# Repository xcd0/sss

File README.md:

# sss

rp2040で作る分割キーボード

- 46キー
- 分割
- カラムスタッガード
- ロータリーエンコーダ
- 狭ピッチ（16.5mm）
- 小型(片手13cmx9cm)
- rp2040
- 3Dプリントケース
- 3Dプリント親指キーキャップ

## 完成予定

## 部品

### rp2040を使用した独自ボード

Raspberry Pi Pico が大きく自作キーボードで使いにくいため、同等のボードを作成した。  
とりあえず名前は安直にRPPslimとした。
[@74th](https://x.com/74th)さんの https://74th.booth.pm/items/3929664 が大変参考になった。  

- 30個のGPIO (Raspberry Pi Picoは23個、ProMicroは18個)
- USB-C
- キースイッチより狭い13.3x50mm (Raspberry Pi Picoは21x51mm)
	- GPIOが余分な場合、カットして13.3x30mmまで小さくして使用できる。
	- 上の写真の左は33mmでカットしている。この状態で17個GPIOを使用できる。
- ただし、GNDの数が少なく、両面実装で分厚く(5mm)、おそらく信頼性が低い。

普通rp2040を使用する自作キーボードは、キーボード本体にrp2040をそのまま実装する場合が多い。  
このsssではrp2040を別基板とし、キーボードに対して垂直に配置することでキーボードのサイズを小さくしている。  
また、別基板とすることで、別のキーボードを作る際にも使いまわせる、rp2040の部分に不具合があっても簡単に置き換えられる、ようにした。
 
### ロータリーエンコーダ

[アリエク](https://ja.aliexpress.com/item/1005006333962313.html)で売っているEVQWGD001という水平のロータリーエンコーダを使用。

### 親指用キーキャップ

 [booth](https://xcd0.booth.pm/items/4510462)に転がしている親指キーキャップの高さを少し高くしたものを使用。

### その他のキーキャップ

[Talp](https://talpkeyboard.net/items/5f5444c380933970d139e98c)さんで売っている0.8Uのキーキャップ。  
大体いつもこれを使っている。

## 設計
handwire予定だったが基板も作ることにした。choc対応をやめたら基板がすっきりして作りやすかった。  
### 回路図

### PCB

## ファームウェアのビルド

[tinygo](https://tinygo.org/)と[tinygo-keyboard](https://github.com/sago35/tinygo-keyboard)を使用している。  

Linuxはディストリビューションごとに方法があるので、<https://tinygo.org/getting-started/install/linux/>を参照。  
Macはhomebrewで入る模様。未確認。<https://tinygo.org/getting-started/install/macos/>  

windowsの場合、<https://tinygo.org/getting-started/install/windows/>にある通り、  
[scoop](https://scoop.sh/)経由でコンパイラをインストールするのが良い。

scoopはpowershellで下記のようにインストールできる。
```pwsh
Set-ExecutionPolicy -ExecutionPolicy RemoteSigned -Scope CurrentUser
Invoke-RestMethod -Uri https://get.scoop.sh | Invoke-Expression
```

後は下記のコマンドで、

```pwsh
scoop install go
scoop install tinygo
scoop install make
```
でコンパイラとmakeをインストールし、

```pwsh
cd src
make
```

でコンパイルできる。

## ファームウェアの書き込み

makefileに書いているため、

```
make flash
```

でビルドしつつ書き込むことができる。  
windowsのwslでは書き込めないので注意。  
powershellやmsysからも書き込める。  
BOOTボタンを押しながら抜き差しする必要はない。  

## キーマップ

goのソースコードに定義するとgofmtでフォーマットされて整列した状態を保てないため、  
[hjson形式](https://hjson.github.io/)で記述し、それをビルド前に解釈してキーマップを返す関数を自動生成するようにしている。  
<./src/script/prebuild/prebuild.go>にビルド前に実行されるコードがある。  

- キーマップ内のキーコードは<https://github.com/sago35/tinygo-keyboard/tree/main/keycodes>にあるものを使用する。  
- `lang`に定義した言語を表す文字列がそのままpackage名として使用される。まあ現状jpしかないけれども。  
- 短縮表現を`define`に定義できるようにした。
- `layout`にはレイヤーごとにキーコードを記載する。
	- これは単純に、`[][]string`として読み込まれ、`,`と`\n`区切りの単純な`[][][]string`に解釈される。

```hjson
# キーマップで使用する言語
lang: jp

# キーマップで使用するキーコードの短縮形定義
define: {
	LSFT: KeyLeftShift
	LCTL: KeyLeftCtrl
	LALT: KeyLeftAlt
}

# キーマップ
# レイヤーごとに記述する。
layout: [
	[ # layer 0
		KeyEsc,      Key1,        Key2,        Key3,        Key4,        Key5,        Key6,      Key7,        Key8,        Key9,        Key0,        KeyMinus,    KeyHat,        KeyBackslash,
		KeyTab,      KeyQ,        KeyW,        KeyE,        KeyR,        KeyT,        KeyY,      KeyU,        KeyI,        KeyO,        KeyP,        KeyAt,       KeyLeftBrace,  KeyBackspace,
		LCTL,        KeyA,        KeyS,        KeyD,        KeyF,        KeyG,        KeyH,      KeyJ,        KeyK,        KeyL,        KeySemicolon,KeyColon,    KeyRightBrace, KeyEnter,
		LSFT,        KeyZ,        KeyX,        KeyC,        KeyV,        KeyB,        KeyN,      KeyM,        KeyComma,    KeyPeriod,   KeySlash,    KeyBackslash2,KeyUp,        KeyRightShift,
		KeyMod1,     KeyHankaku,  KeyWindows,  LALT,        KeyMuhenkan, KeySpace,    KeySpace,  KeyHenkan,   KeyHiragana, KeyLeftAlt,  KeyMod1,     KeyLeft,     KeyDown,       KeyRight,
	]
```

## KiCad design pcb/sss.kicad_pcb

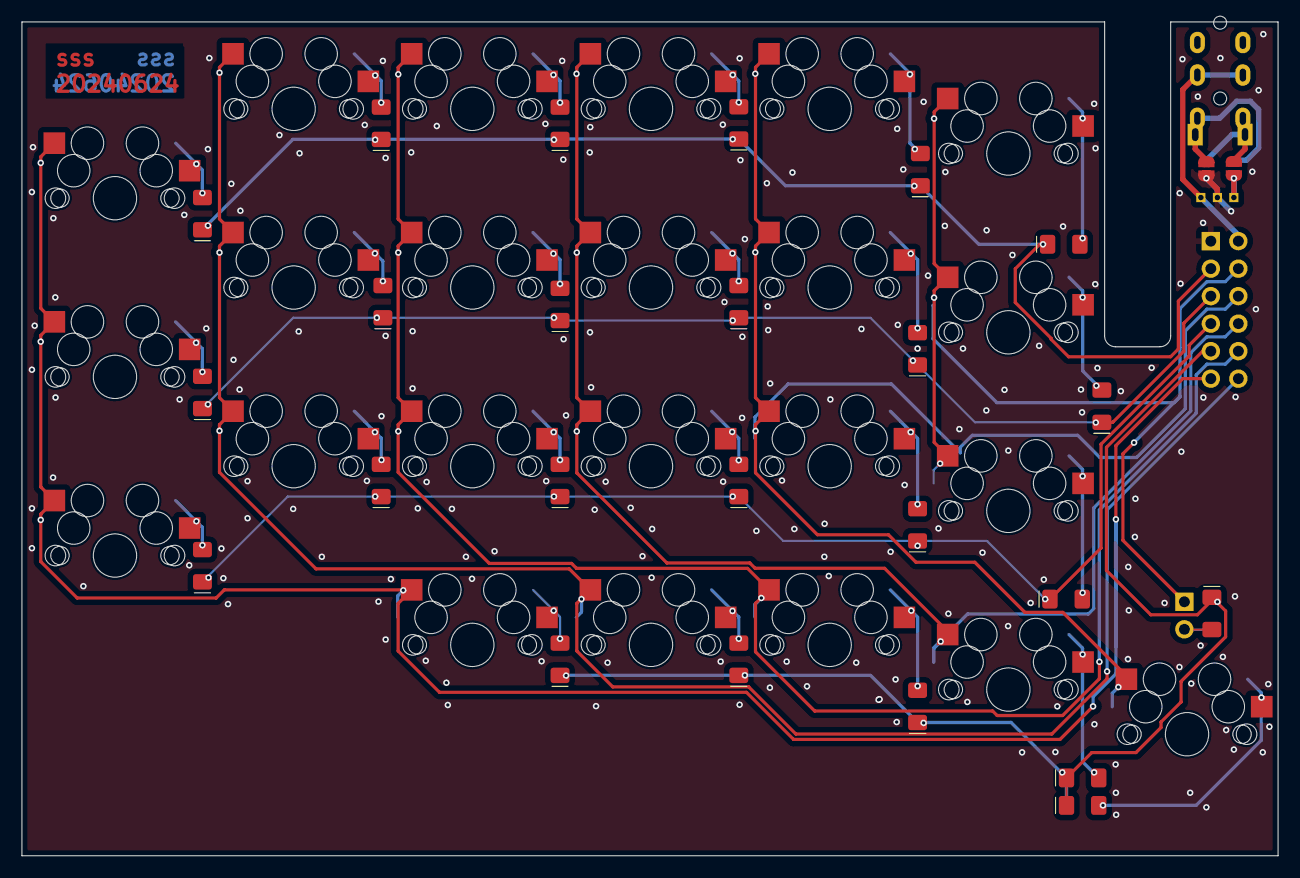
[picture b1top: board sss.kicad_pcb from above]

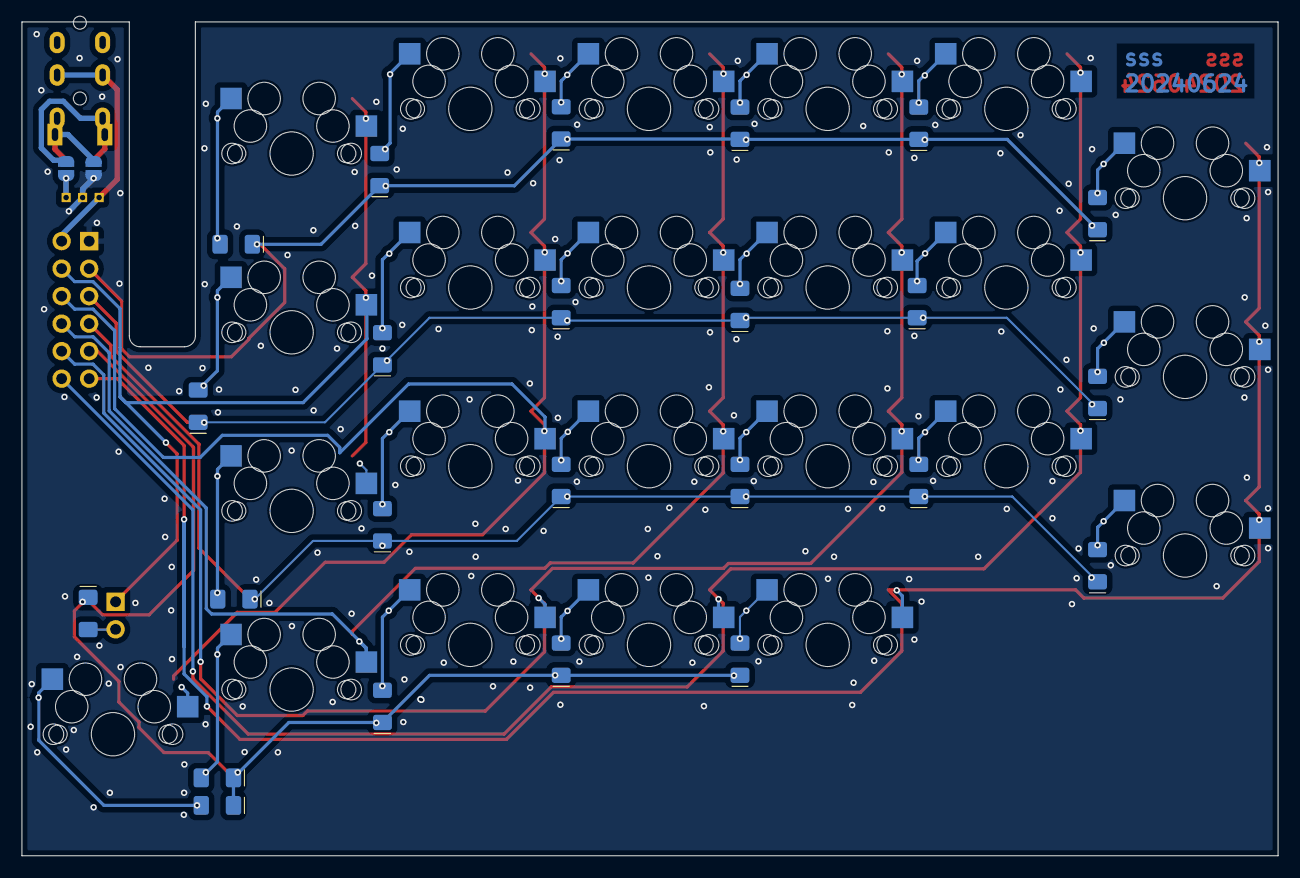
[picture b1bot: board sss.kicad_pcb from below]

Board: 2 copper layers, 116.0 x 77.0 mm, 54 parts (2 on the bottom side), 39 nets.

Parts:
D1, D2, D3, D4, D5, D6, D7, D8, D9, D10, D11, D12, D13, D14, D15, D16, D17, D18, D19, D20, D21, D22, D23, D24: D; ll
J1: AudioJack4; MJ-4PP-9
JP1, JP2, JP3, JP4: Jumper_2_Open; SolderJumper-2_P1.3mm_Open_RoundedPad1.0x1.5mm
SW1, SW2, SW3, SW4, SW5, SW6, SW7, SW8, SW9, SW10, SW11, SW12, SW13, SW14, SW15, SW16, SW17, SW18, SW20, SW21, SW22, SW23, SW24: SW_Push; CherryMX_HotSwap_Narrow
SW19: SW_Push; PinHeader_1x02_P2.54mm_Vertical
U1: PinHeader_2x06_P2.54mm_Vertical

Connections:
GND: JP1.2 (B), JP3.2 (B), U1.1 (GND)
GND_in: J1.S, JP1.1 (A), JP3.1 (A)
unnamed: D1.2 (A), SW1.2
unnamed: D2.2 (A), SW2.2
unnamed: D3.2 (A), SW3.2
unnamed: D4.2 (A), SW4.2
unnamed: D5.2 (A), SW5.2
unnamed: D6.2 (A), SW6.2
unnamed: D7.2 (A), SW7.2
unnamed: D8.2 (A), SW8.2
unnamed: D9.2 (A), SW9.2
unnamed: D10.2 (A), SW10.2
unnamed: D11.2 (A), SW11.2
unnamed: D12.2 (A), SW12.2
unnamed: D13.2 (A), SW13.2
unnamed: D14.2 (A), SW14.2
unnamed: D15.2 (A), SW15.2
unnamed: D16.2 (A), SW16.2
unnamed: D17.2 (A), SW17.2
unnamed: D18.2 (A), SW18.2
unnamed: D19.2 (A), SW19.2
unnamed: D20.2 (A), SW20.2
unnamed: D21.2 (A), SW21.2
unnamed: D22.2 (A), SW22.2
unnamed: D23.2 (A), SW23.2
unnamed: D24.2 (A), SW24.2
VCC: JP2.2 (B), JP4.2 (B)
VCC_in: J1.T, JP2.1 (A), JP4.1 (A)
col0: SW1.1, SW7.1, SW13.1, SW19.1, U1.8 (GPIO06/SPI0_SCK/UART1_CTS/I2C1_SDA/PWM3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)
col1: SW2.1, SW8.1, SW14.1, SW20.1, U1.9 (GPIO07/SPI0_TX_/UART1_RTS/I2C1_SCL/PWM3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)
col2: SW3.1, SW9.1, SW15.1, SW21.1, U1.10 (GPIO08/SPI1_RX_/UART1_TX_/I2C0_SDA/PWM4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)
col3: SW4.1, SW10.1, SW16.1, SW22.1, U1.11
col4: SW5.1, SW11.1, SW17.1, SW23.1, U1.12
col5: SW6.1, SW12.1, SW18.1, SW24.1, U1.6 (GPIO04/SPI0_RX_/UART1_TX_/I2C0_SDA/PWM2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)
data: J1.R1, U1.7 (GPIO05/SPI0_CSn/UART1_RX_/I2C0_SCL/PWM2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)
row0: D1.1 (K), D2.1 (K), D3.1 (K), D4.1 (K), D5.1 (K), D6.1 (K), U1.2 (GPIO00/SPI0_RX_/UART0_TX_/I2C0_SDA/PWM0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)
row1: D7.1 (K), D8.1 (K), D9.1 (K), D10.1 (K), D11.1 (K), D12.1 (K), U1.3 (GPIO01/SPI0_CSn/UART0_RX_/I2C0_SCL/PWM0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)
row2: D13.1 (K), D14.1 (K), D15.1 (K), D16.1 (K), D17.1 (K), D18.1 (K), U1.4 (GPIO02/SPI0_SCK/UART0_CTS/I2C1_SDA/PWM1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)
row3: D19.1 (K), D20.1 (K), D21.1 (K), D22.1 (K), D23.1 (K), D24.1 (K), U1.5 (GPIO03/SPI0_TX_/UART0_RTS/I2C1_SCL/PWM1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)

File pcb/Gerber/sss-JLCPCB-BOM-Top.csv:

Comment,Designator,Footprint,JLCPCB Part#,MFR.Part#,Qty
"SW_Push","SW20,SW17,SW7,SW4,SW3,SW16,SW21,SW10,SW14,SW13,SW1,SW11,SW12,SW8,SW22,SW23,SW5,SW2,SW18,SW6,SW15,SW9,SW24","CherryMX_HotSwap_Narrow","","",23
"D","D3,D24,D7,D15,D5,D6,D4,D1,D23,D16,D11,D21,D10,D20,D2,D12,D22,D18,D9,D17,D19,D8,D13,D14","ll","","",24

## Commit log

2024-08-02 fix: update makefile
